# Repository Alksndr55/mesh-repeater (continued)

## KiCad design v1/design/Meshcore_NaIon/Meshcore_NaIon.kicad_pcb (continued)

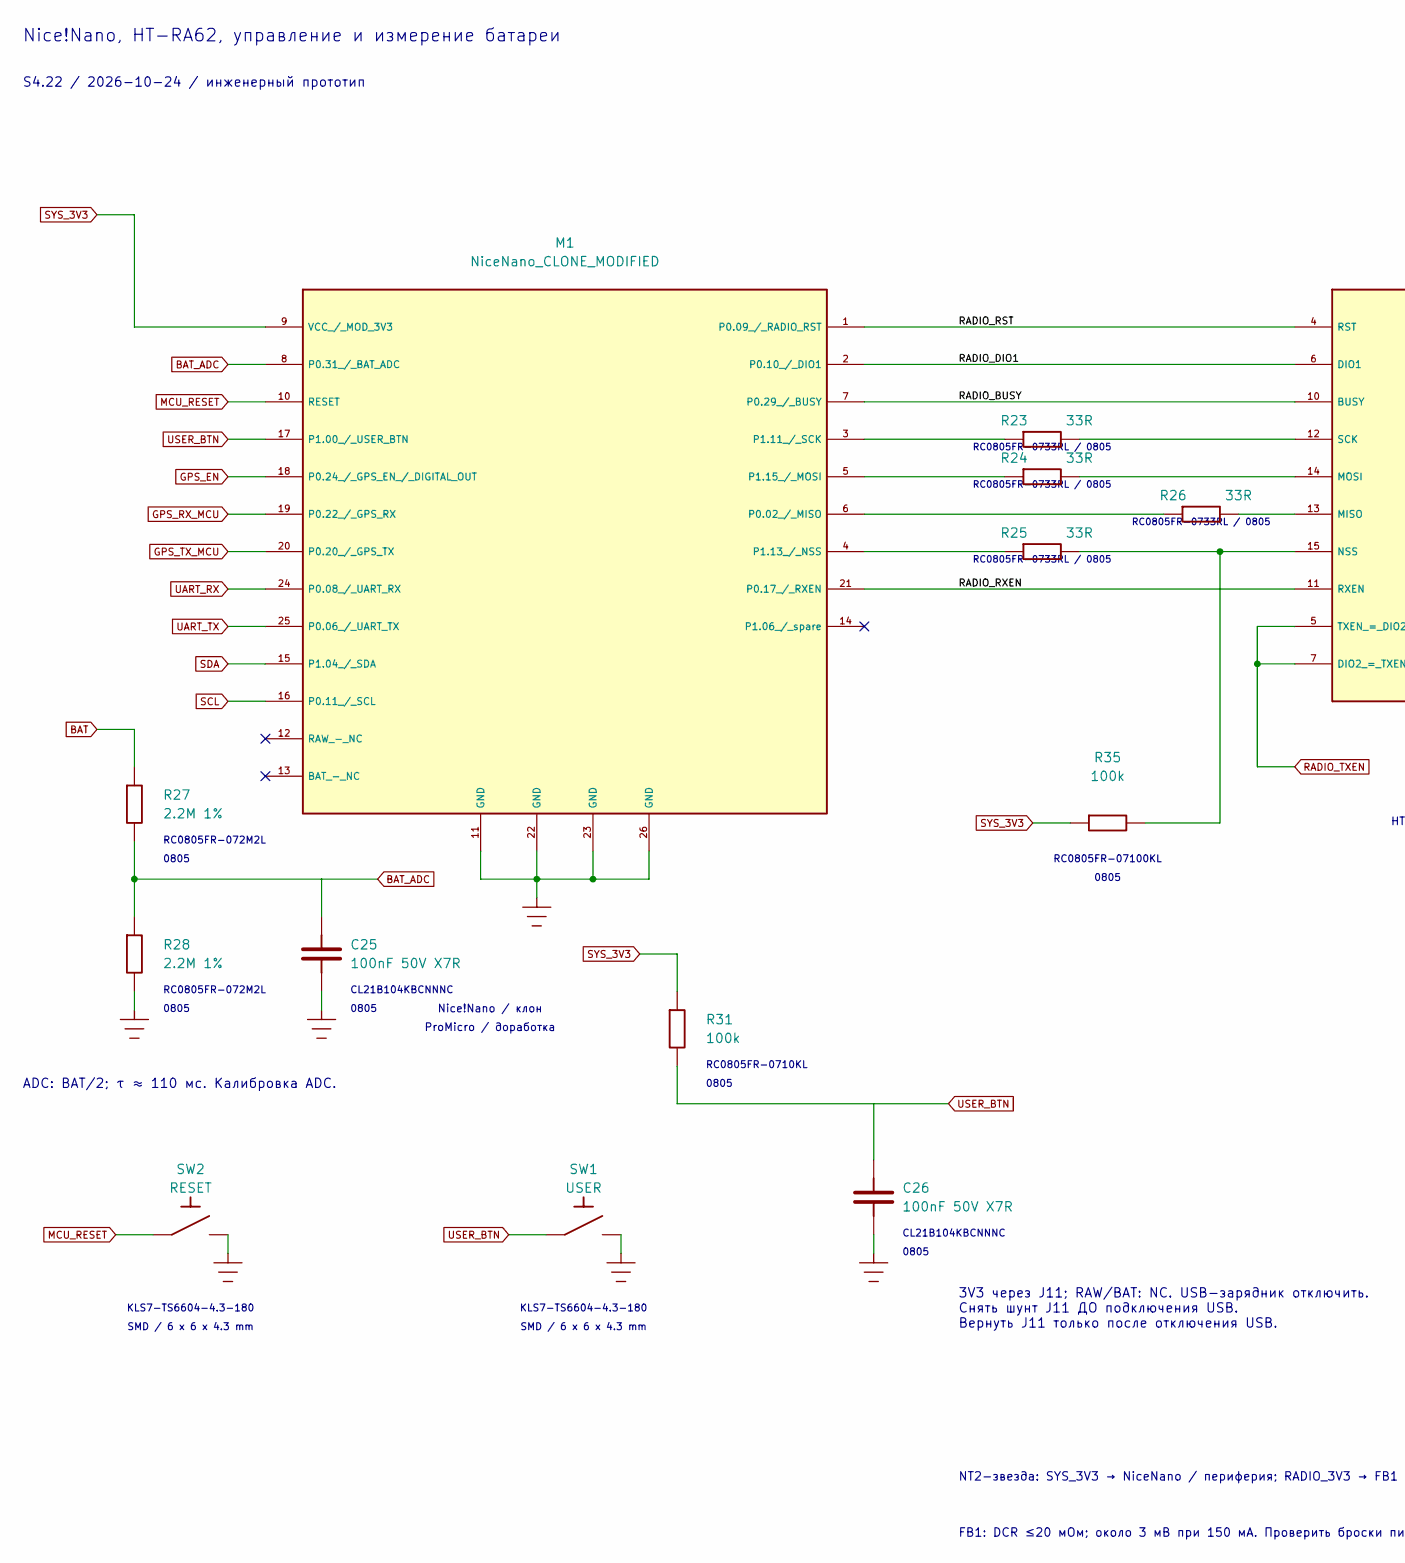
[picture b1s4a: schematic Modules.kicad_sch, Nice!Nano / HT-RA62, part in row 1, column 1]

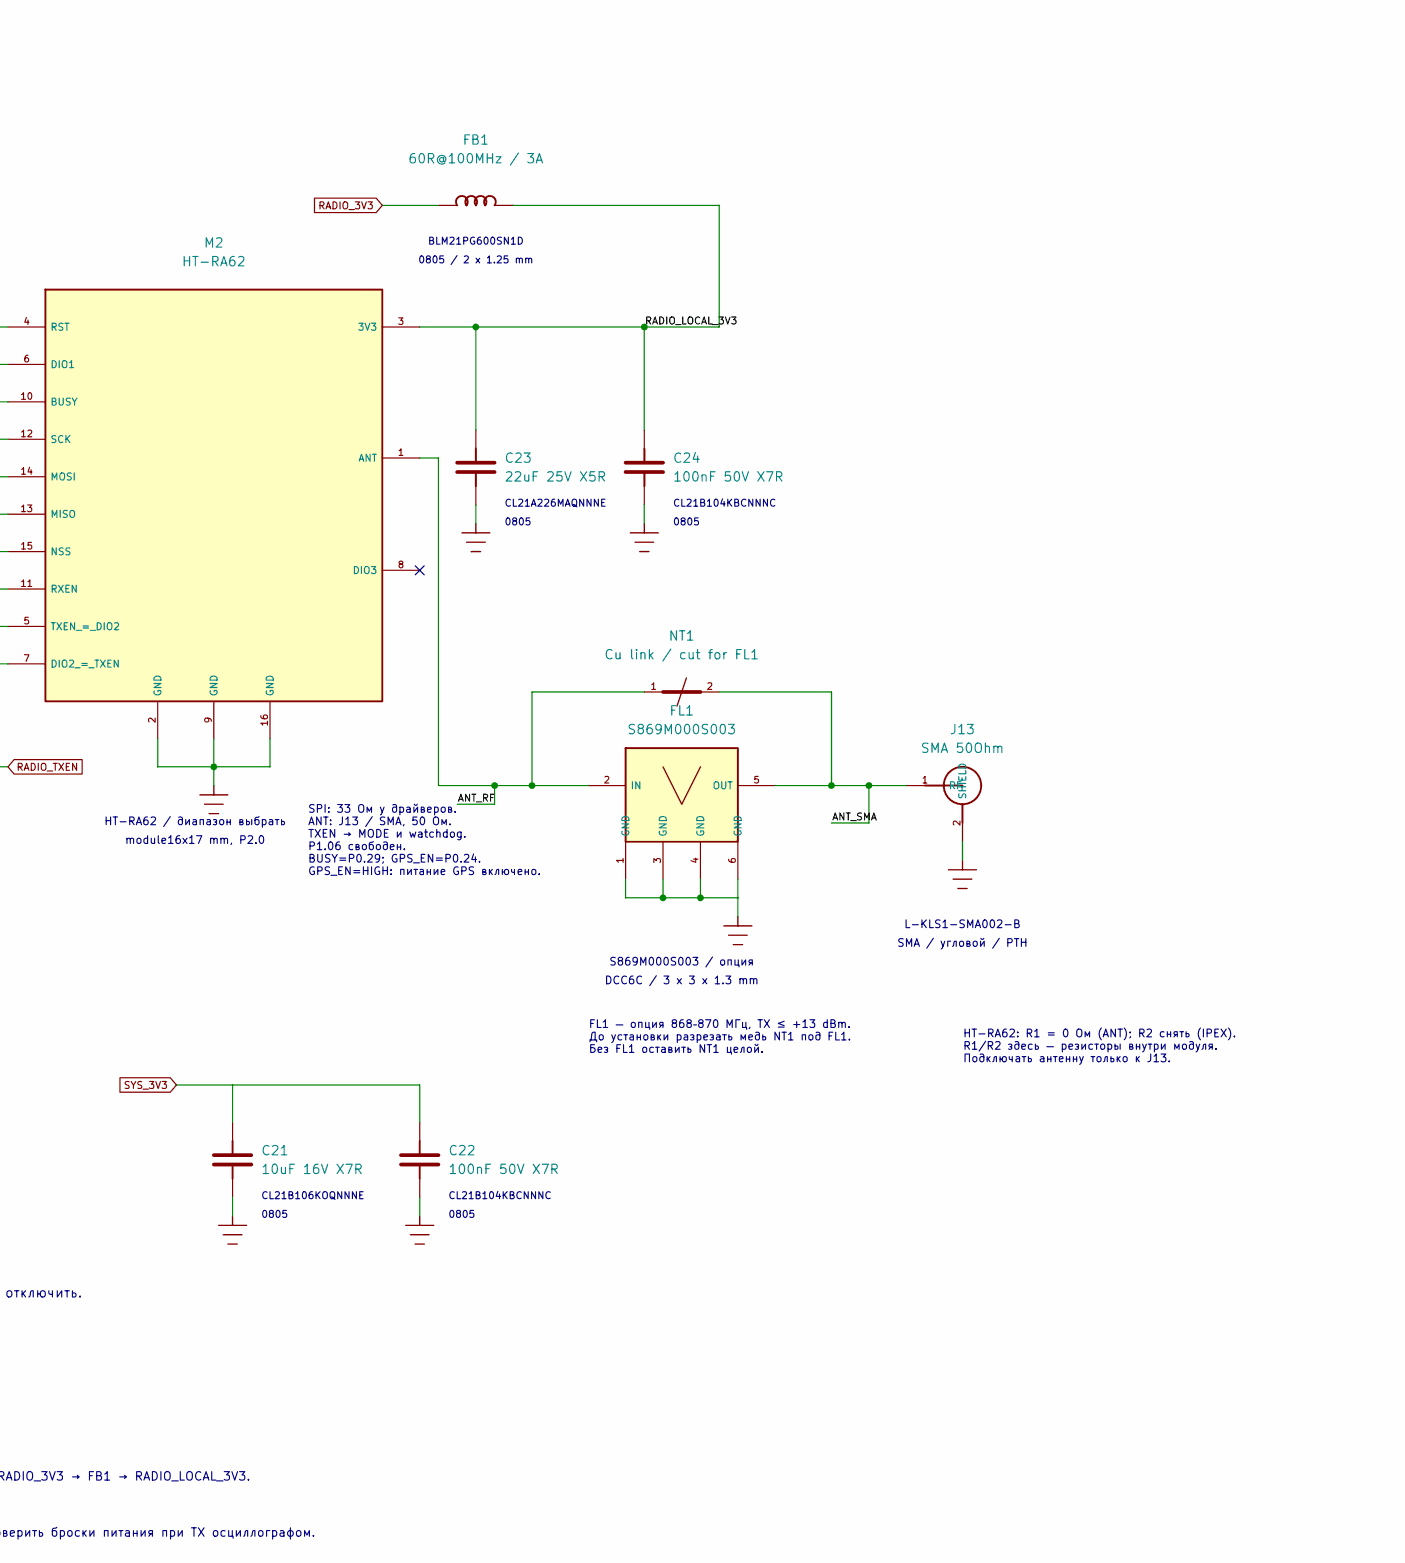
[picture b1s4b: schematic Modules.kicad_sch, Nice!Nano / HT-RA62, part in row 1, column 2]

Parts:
C21: 10uF 16V X7R; C_0805_2012Metric; MPN CL21B106KOQNNNE
C22, C24, C25, C26: 100nF 50V X7R; C_0805_2012Metric; MPN CL21B104KBCNNNC
C23: 22uF 25V X5R; C_0805_2012Metric; MPN CL21A226MAQNNNE
FB1: 60R@100MHz / 3A; Ferrite_Murata_BLM21PG; MPN BLM21PG600SN1D
FL1: S869M000S003; SAW_AEL_DCC6C_S869M000S003; MPN S869M000S003
J13: SMA 50Ohm; SMA_KLS1_SMA002_B_Horizontal; MPN L-KLS1-SMA002-B
M1: NiceNano_CLONE_MODIFIED; NiceNano_13x2_Socket; MPN User supplied NiceNano clone
M2: HT-RA62; HT_RA62; MPN HT-RA62 band variant TBD
NT1: Cu link / cut for FL1; RF_Cut_Link_0p6; MPN PCB copper / not purchased
R23, R24, R25, R26: 33R; R_0805_2012Metric; MPN RC0805FR-0733RL
R27, R28: 2.2M 1%; R_0805_2012Metric; MPN RC0805FR-072M2L
R31, R35: 100k; R_0805_2012Metric; MPN RC0805FR-07100KL
SW1: USER; SW_Push_KLS7_TS6604_4_3_180; MPN KLS7-TS6604-4.3-180
SW2: RESET; SW_Push_KLS7_TS6604_4_3_180; MPN KLS7-TS6604-4.3-180

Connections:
/3. Modules/ANT_RF: FL1.2 (IN), M2.1 (ANT), NT1.1 (A)
/3. Modules/ANT_SMA: FL1.5 (OUT), J13.1 (SIGNAL), NT1.2 (B)
/3. Modules/RADIO_BUSY: M1.7 (P0.29_/_BUSY), M2.10 (BUSY_10)
/3. Modules/RADIO_DIO1: M1.2 (P0.10_/_DIO1), M2.6 (DIO1_6)
/3. Modules/RADIO_LOCAL_3V3: C23.1, C24.1, FB1.2, M2.3 (3V3_3)
/3. Modules/RADIO_RST: M1.1 (P0.09_/_RADIO_RST), M2.4 (RST_4)
/3. Modules/RADIO_RXEN: M1.21 (P0.17_/_RXEN), M2.11 (RXEN_11)
BAT: R27.1; also elsewhere on the board
BAT_ADC: C25.1, M1.8 (P0.31_/_BAT_ADC), R27.2, R28.1
GND: C21.2, C22.2, C23.2, C24.2, C25.2, C26.2, FL1.1 (GND), FL1.3 (GND), FL1.4 (GND), FL1.6 (GND), J13.2 (GND), M1.11 (GND), M1.22 (GND), M1.23 (GND), M1.26 (GND), M2.2 (GND_2), M2.9 (GND_9), M2.16 (GND_16), R28.2, SW1.2, SW2.2; also elsewhere on the board
GPS_EN: M1.18 (P0.24_/_GPS_EN_/_DIGITAL_OUT); also elsewhere on the board
GPS_RX_MCU: M1.19 (P0.22_/_GPS_RX); also elsewhere on the board
GPS_TX_MCU: M1.20 (P0.20_/_GPS_TX); also elsewhere on the board
MCU_RESET: M1.10 (RESET), SW2.1; also elsewhere on the board
unnamed: M1.6 (P0.02_/_MISO), R26.2
unnamed: M1.3 (P1.11_/_SCK), R23.1
unnamed: M1.4 (P1.13_/_NSS), R25.1
unnamed: M1.5 (P1.15_/_MOSI), R24.1
unnamed: M2.13 (MISO_13), R26.1
unnamed: M2.14 (MOSI_14), R24.2
unnamed: M2.15 (NSS_15), R25.2, R35.2
unnamed: M2.12 (SCK_12), R23.2
RADIO_3V3: FB1.1; also elsewhere on the board
RADIO_TXEN: M2.5 (TXEN_=_DIO2_5), M2.7 (DIO2_=_TXEN_7); also elsewhere on the board
SCL: M1.16 (P0.11_/_SCL); also elsewhere on the board
SDA: M1.15 (P1.04_/_SDA); also elsewhere on the board
SYS_3V3: C21.1, C22.1, M1.9 (VCC_/_MOD_3V3), R31.1, R35.1; also elsewhere on the board
UART_RX: M1.24 (P0.08_/_UART_RX); also elsewhere on the board
UART_TX: M1.25 (P0.06_/_UART_TX); also elsewhere on the board
USER_BTN: C26.1, M1.17 (P1.00_/_USER_BTN), R31.2, SW1.1

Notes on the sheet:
FB1: DCR ≤20 мОм; около 3 мВ при 150 мА. Проверить броски питания при TX осциллографом.
HT-RA62: R1 = 0 Ом (ANT); R2 снять (IPEX). R1/R2 здесь — резисторы внутри модуля. Подключать антенну только к J13.
SMA / угловой / PTH
FL1 — опция 868–870 МГц, TX ≤ +13 dBm. До установки разрезать медь NT1 под FL1. Без FL1 оставить NT1 целой.
KLS7-TS6604-4.3-180
BLM21PG600SN1D
0805
RC0805FR-0733RL / 0805
SMD / 6 x 6 x 4.3 mm
module16x17 mm, P2.0
S869M000S003 / опция
CL21B104KBCNNNC
CL21B106KOQNNNE
SPI: 33 Ом у драйверов. ANT: J13 / SMA, 50 Ом. TXEN → MODE и watchdog. P1.06 свободен. BUSY=P0.29; GPS_EN=P0.24. GPS_EN=HIGH: питание GPS включено.
DCC6C / 3 x 3 x 1.3 mm
3V3 через J11; RAW/BAT: NC. USB-зарядник отключить. Снять шунт J11 ДО подключения USB. Вернуть J11 только после отключения USB.
L-KLS1-SMA002-B
ADC: BAT/2; τ ≈ 110 мс. Калибровка ADC.
Nice!Nano, HT-RA62, управление и измерение батареи
S4.22 / 2026-10-24 / инженерный прототип
CL21A226MAQNNNE
RC0805FR-072M2L
HT-RA62 / диапазон выбрать
NT2-звезда: SYS_3V3 → NiceNano / периферия; RADIO_3V3 → FB1 → RADIO_LOCAL_3V3.
RC0805FR-0710KL
Nice!Nano / клон
RC0805FR-07100KL
ProMicro / доработка
0805 / 2 x 1.25 mm

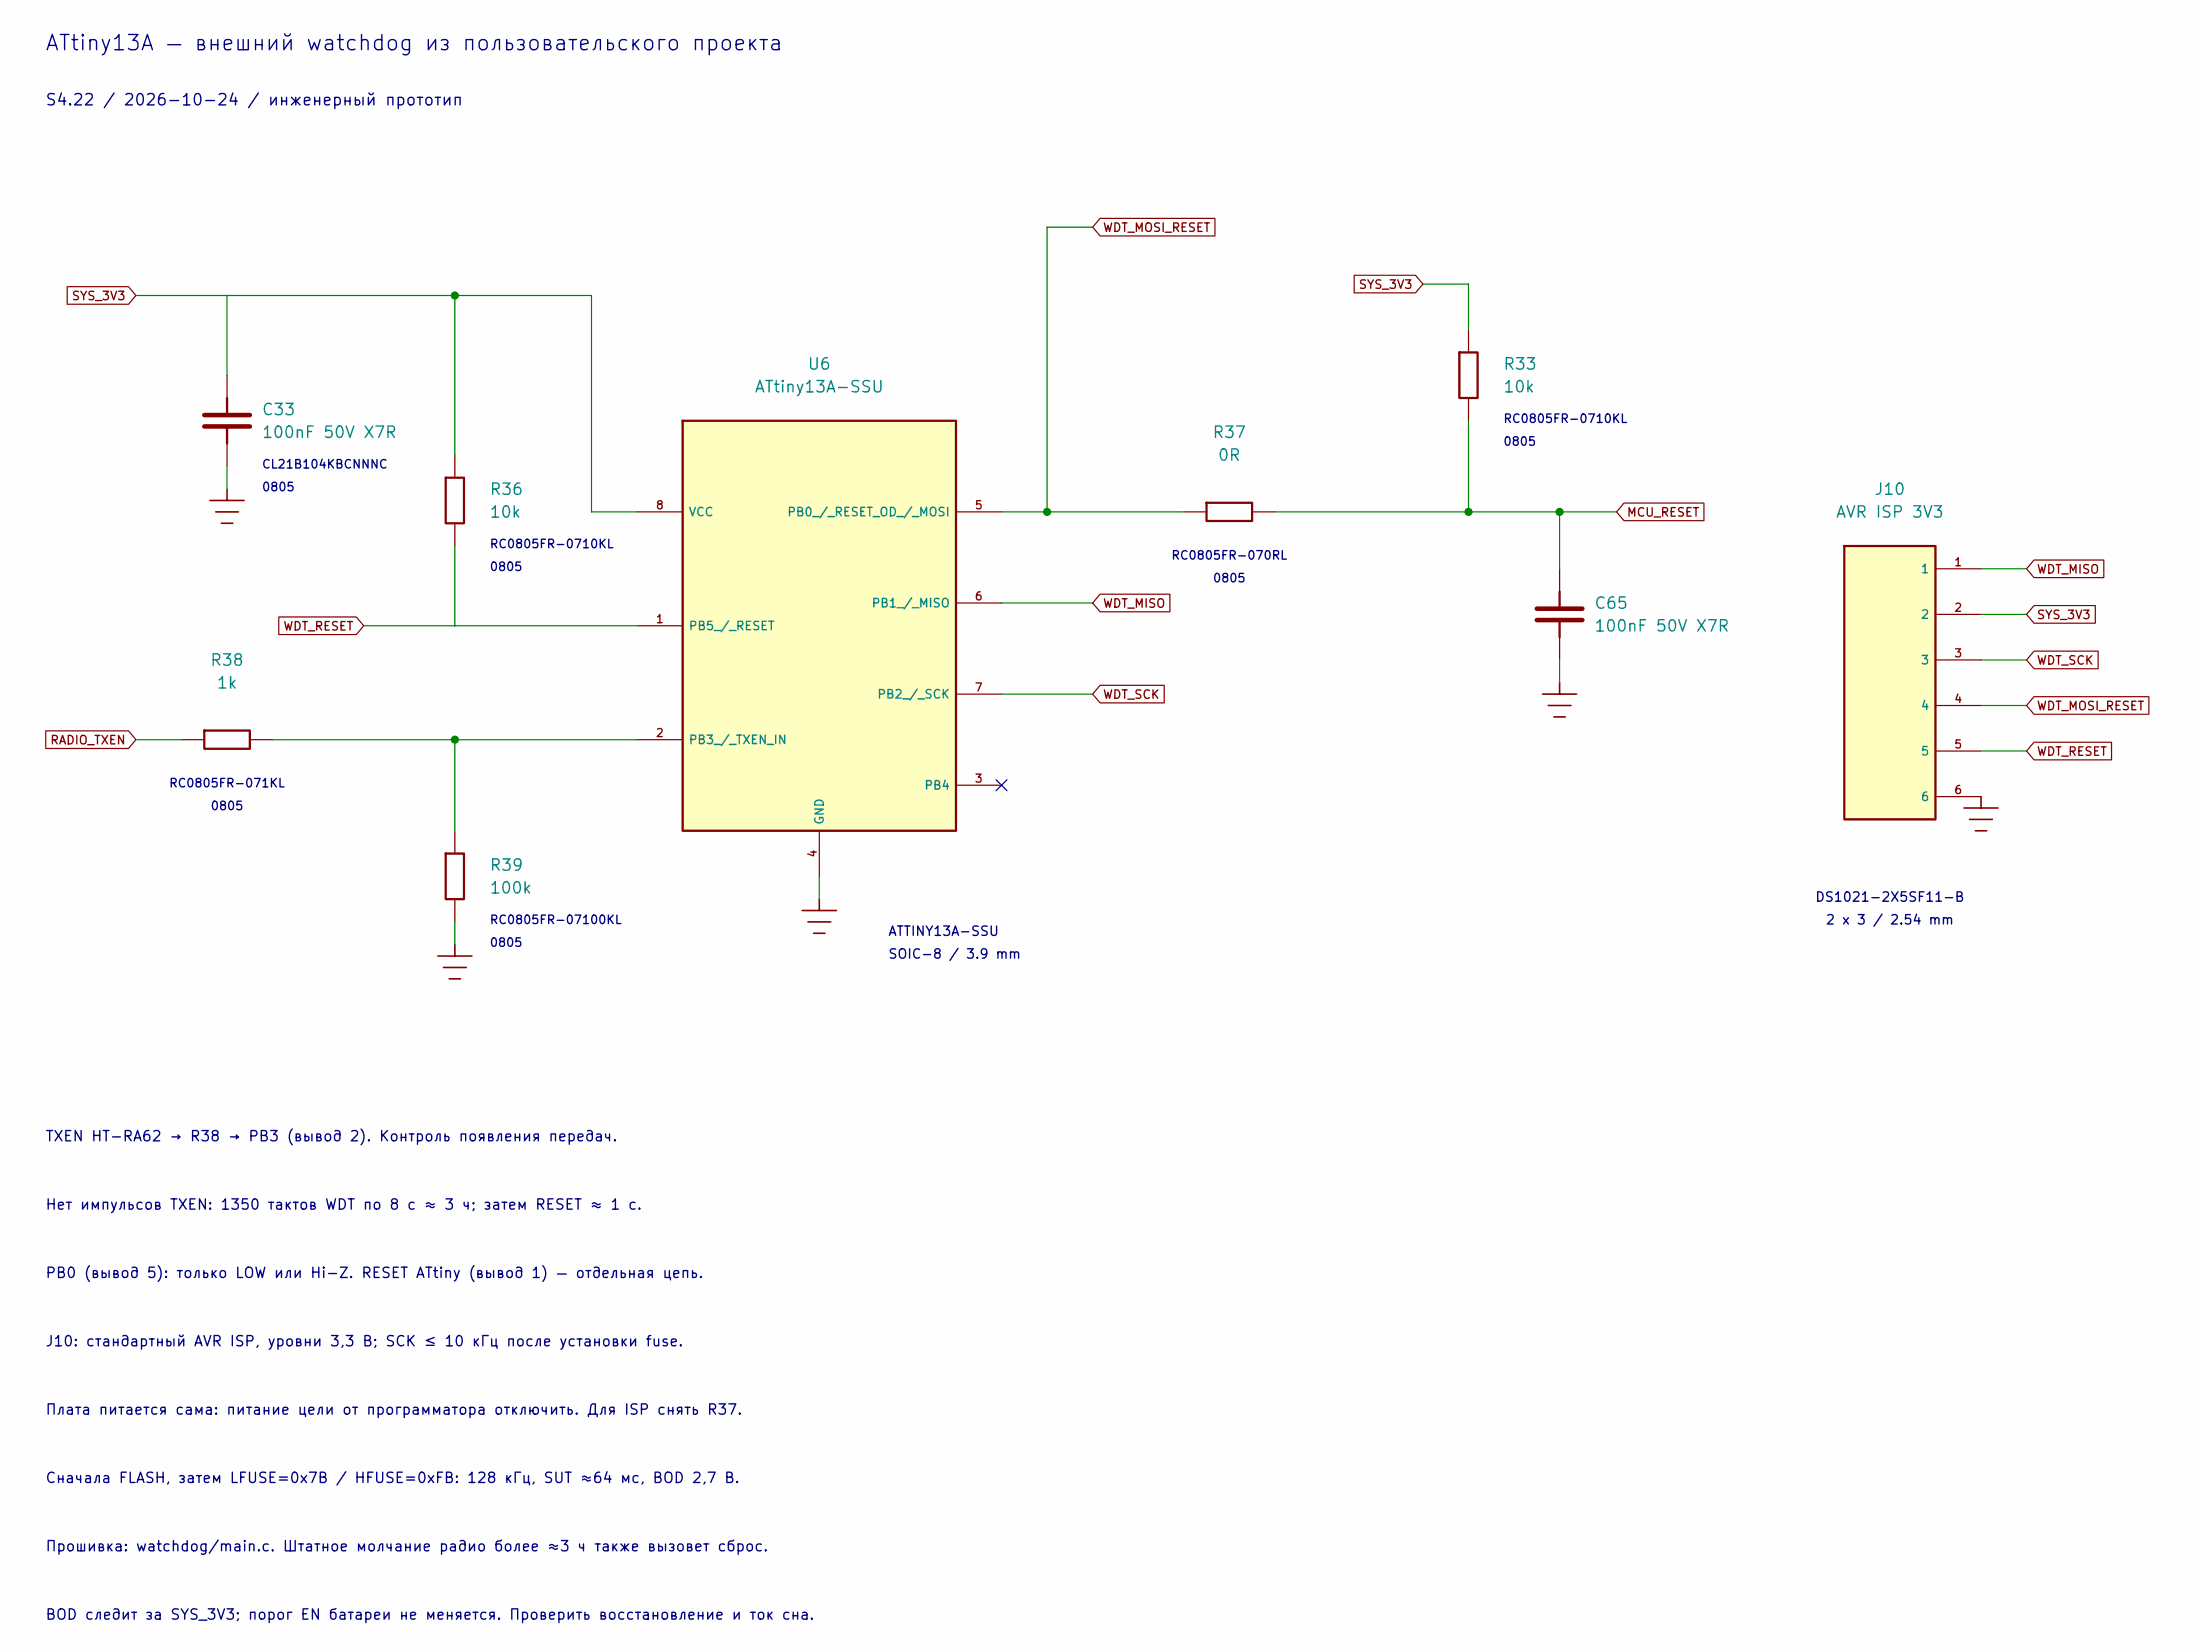
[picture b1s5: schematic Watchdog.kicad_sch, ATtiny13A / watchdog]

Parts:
C33, C65: 100nF 50V X7R; C_0805_2012Metric; MPN CL21B104KBCNNNC
J10: AVR ISP 3V3; PinHeader_2x03_P2.54mm_Vertical; MPN DS1021-2X5SF11-B
R33, R36: 10k; R_0805_2012Metric; MPN RC0805FR-0710KL
R37: 0R; R_0805_2012Metric; MPN RC0805FR-070RL
R38: 1k; R_0805_2012Metric; MPN RC0805FR-071KL
R39: 100k; R_0805_2012Metric; MPN RC0805FR-07100KL
U6: ATtiny13A-SSU; SOIC-8_3.9x4.9mm_P1.27mm; MPN ATTINY13A-SSU

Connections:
GND: C33.2, C65.2, J10.6, R39.2, U6.4 (GND); also elsewhere on the board
MCU_RESET: C65.1, R33.2, R37.2; also elsewhere on the board
unnamed: R38.2, R39.1, U6.2 (PB3_/_TXEN_IN)
RADIO_TXEN: R38.1; also elsewhere on the board
SYS_3V3: C33.1, J10.2, R33.1, R36.1, U6.8 (VCC); also elsewhere on the board
WDT_MISO: J10.1, U6.6 (PB1_/_MISO)
WDT_MOSI_RESET: J10.4, R37.1, U6.5 (PB0_/_RESET_OD_/_MOSI)
WDT_RESET: J10.5, R36.2, U6.1 (PB5_/_RESET)
WDT_SCK: J10.3, U6.7 (PB2_/_SCK)

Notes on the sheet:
PB0 (вывод 5): только LOW или Hi-Z. RESET ATtiny (вывод 1) — отдельная цепь.
ATtiny13A — внешний watchdog из пользовательского проекта
0805
RC0805FR-07100KL
Плата питается сама: питание цели от программатора отключить. Для ISP снять R37.
RC0805FR-070RL
SOIC-8 / 3.9 mm
TXEN HT-RA62 → R38 → PB3 (вывод 2). Контроль появления передач.
ATTINY13A-SSU
J10: стандартный AVR ISP, уровни 3,3 В; SCK ≤ 10 кГц после установки fuse.
DS1021-2X5SF11-B
BOD следит за SYS_3V3; порог EN батареи не меняется. Проверить восстановление и ток сна.
CL21B104KBCNNNC
RC0805FR-071KL
RC0805FR-0710KL
Сначала FLASH, затем LFUSE=0x7B / HFUSE=0xFB: 128 кГц, SUT ≈64 мс, BOD 2,7 В.
S4.22 / 2026-10-24 / инженерный прототип
2 x 3 / 2.54 mm
Прошивка: watchdog/main.c. Штатное молчание радио более ≈3 ч также вызовет сброс.
Нет импульсов TXEN: 1350 тактов WDT по 8 с ≈ 3 ч; затем RESET ≈ 1 с.

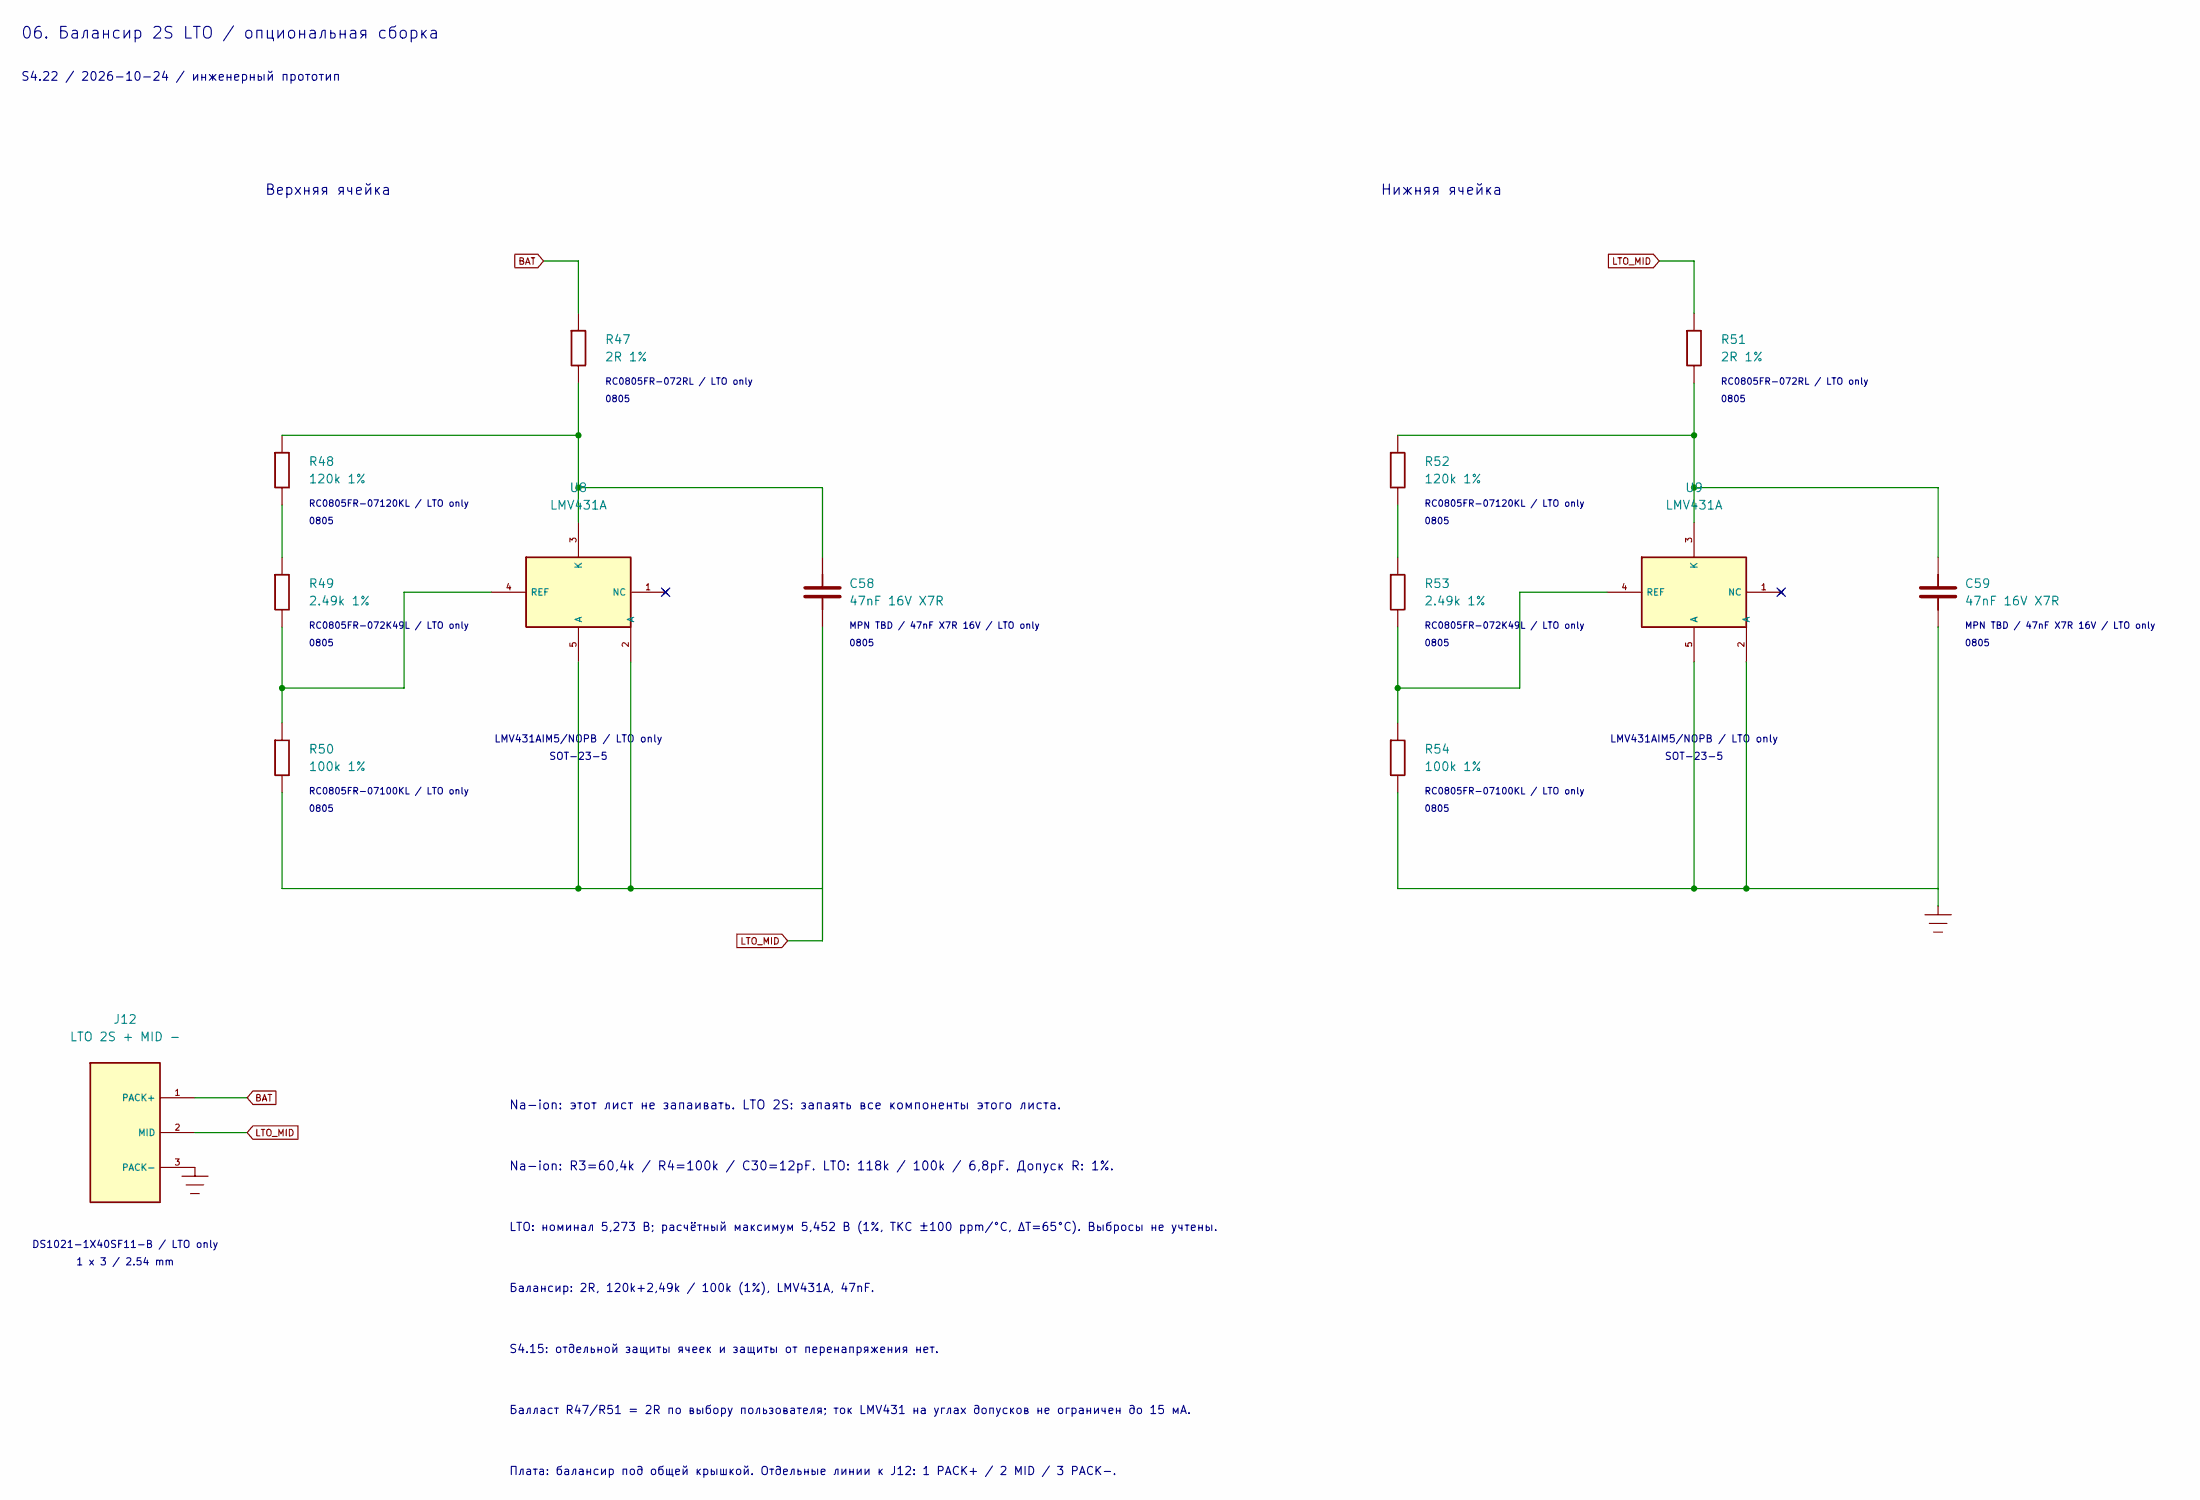
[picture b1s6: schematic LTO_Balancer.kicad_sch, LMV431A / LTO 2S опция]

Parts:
C58, C59: 47nF 16V X7R; C_0805_2012Metric; MPN MPN TBD / 47nF X7R 16V
J12: LTO 2S + MID -; PinHeader_1x03_P2.54mm_Vertical; MPN DS1021-1X40SF11-B
R47, R51: 2R 1%; R_0805_2012Metric; MPN RC0805FR-072RL; LCSC C110775
R48, R52: 120k 1%; R_0805_2012Metric; MPN RC0805FR-07120KL; LCSC C110775
R49, R53: 2.49k 1%; R_0805_2012Metric; MPN RC0805FR-072K49L; LCSC C110775
R50, R54: 100k 1%; R_0805_2012Metric; MPN RC0805FR-07100KL; LCSC C110775
U8, U9: LMV431A; SOT-23-5; MPN LMV431AIM5/NOPB

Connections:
BAT: J12.1 (PACK+), R47.1; also elsewhere on the board
GND: C59.2, J12.3 (PACK-), R54.2, U9.2 (A), U9.5 (A); also elsewhere on the board
LTO_MID: C58.2, J12.2 (MID), R50.2, R51.1, U8.2 (A), U8.5 (A)
unnamed: R48.2, R49.1
unnamed: R52.2, R53.1
unnamed: C58.1, R47.2, R48.1, U8.3 (K)
unnamed: R49.2, R50.1, U8.4 (REF)
unnamed: C59.1, R51.2, R52.1, U9.3 (K)
unnamed: R53.2, R54.1, U9.4 (REF)

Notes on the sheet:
0805
LMV431AIM5/NOPB / LTO only
MPN TBD / 47nF X7R 16V / LTO only
RC0805FR-07120KL / LTO only
RC0805FR-072K49L / LTO only
SOT-23-5
RC0805FR-07100KL / LTO only
1 x 3 / 2.54 mm
Верхняя ячейка
S4.15: отдельной защиты ячеек и защиты от перенапряжения нет.
S4.22 / 2026-10-24 / инженерный прототип
06. Балансир 2S LTO / опциональная сборка
Балансир: 2R, 120k+2,49k / 100k (1%), LMV431A, 47nF.
RC0805FR-072RL / LTO only
Плата: балансир под общей крышкой. Отдельные линии к J12: 1 PACK+ / 2 MID / 3 PACK-.
LTO: номинал 5,273 В; расчётный максимум 5,452 В (1%, ТКС ±100 ppm/°C, ΔT=65°C). Выбросы не учтены.
Нижняя ячейка
DS1021-1X40SF11-B / LTO only
Балласт R47/R51 = 2R по выбору пользователя; ток LMV431 на углах допусков не ограничен до 15 мА.
Na-ion: R3=60,4k / R4=100k / C30=12pF. LTO: 118k / 100k / 6,8pF. Допуск R: 1%.
Na-ion: этот лист не запаивать. LTO 2S: запаять все компоненты этого листа.

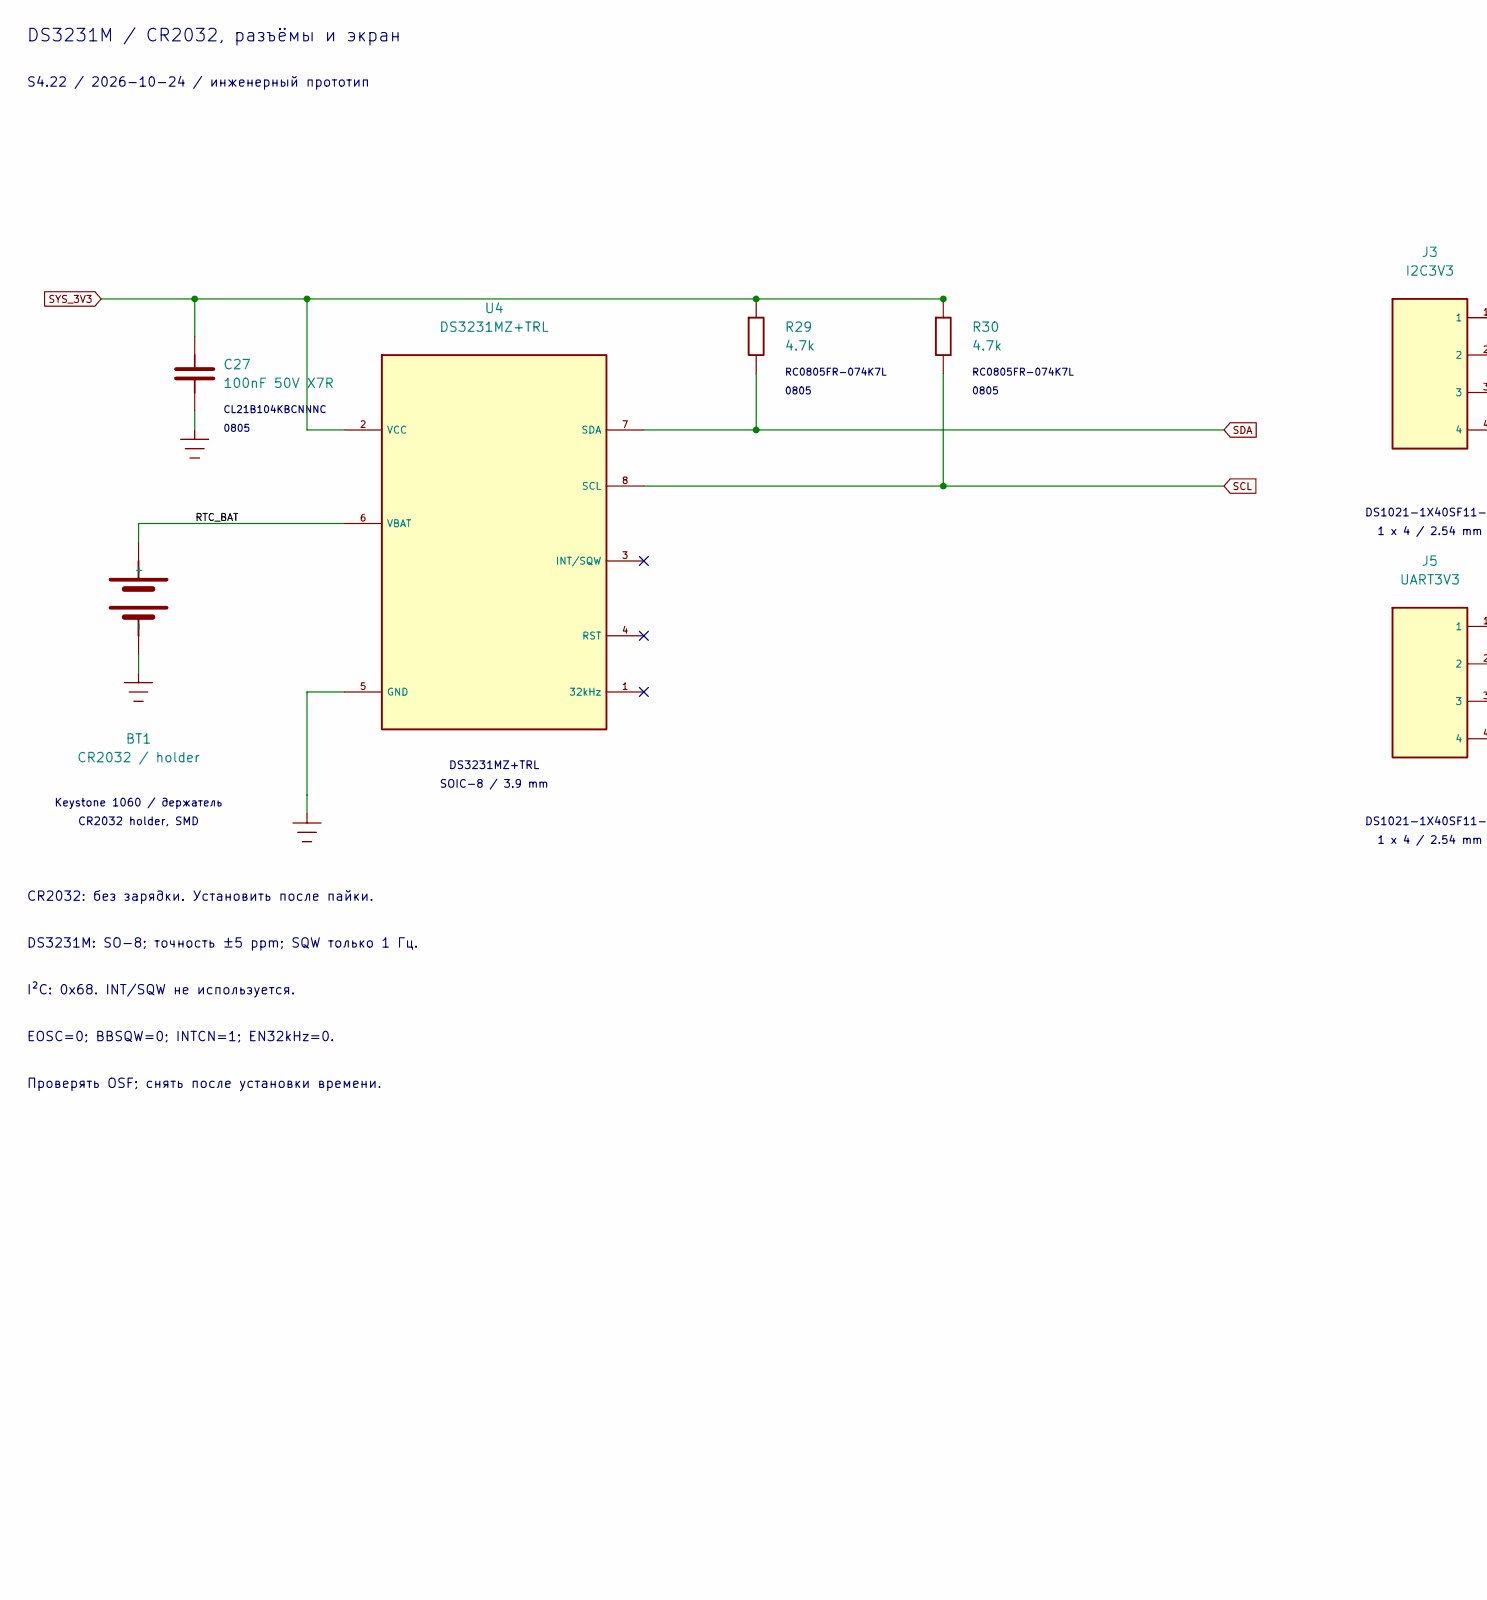
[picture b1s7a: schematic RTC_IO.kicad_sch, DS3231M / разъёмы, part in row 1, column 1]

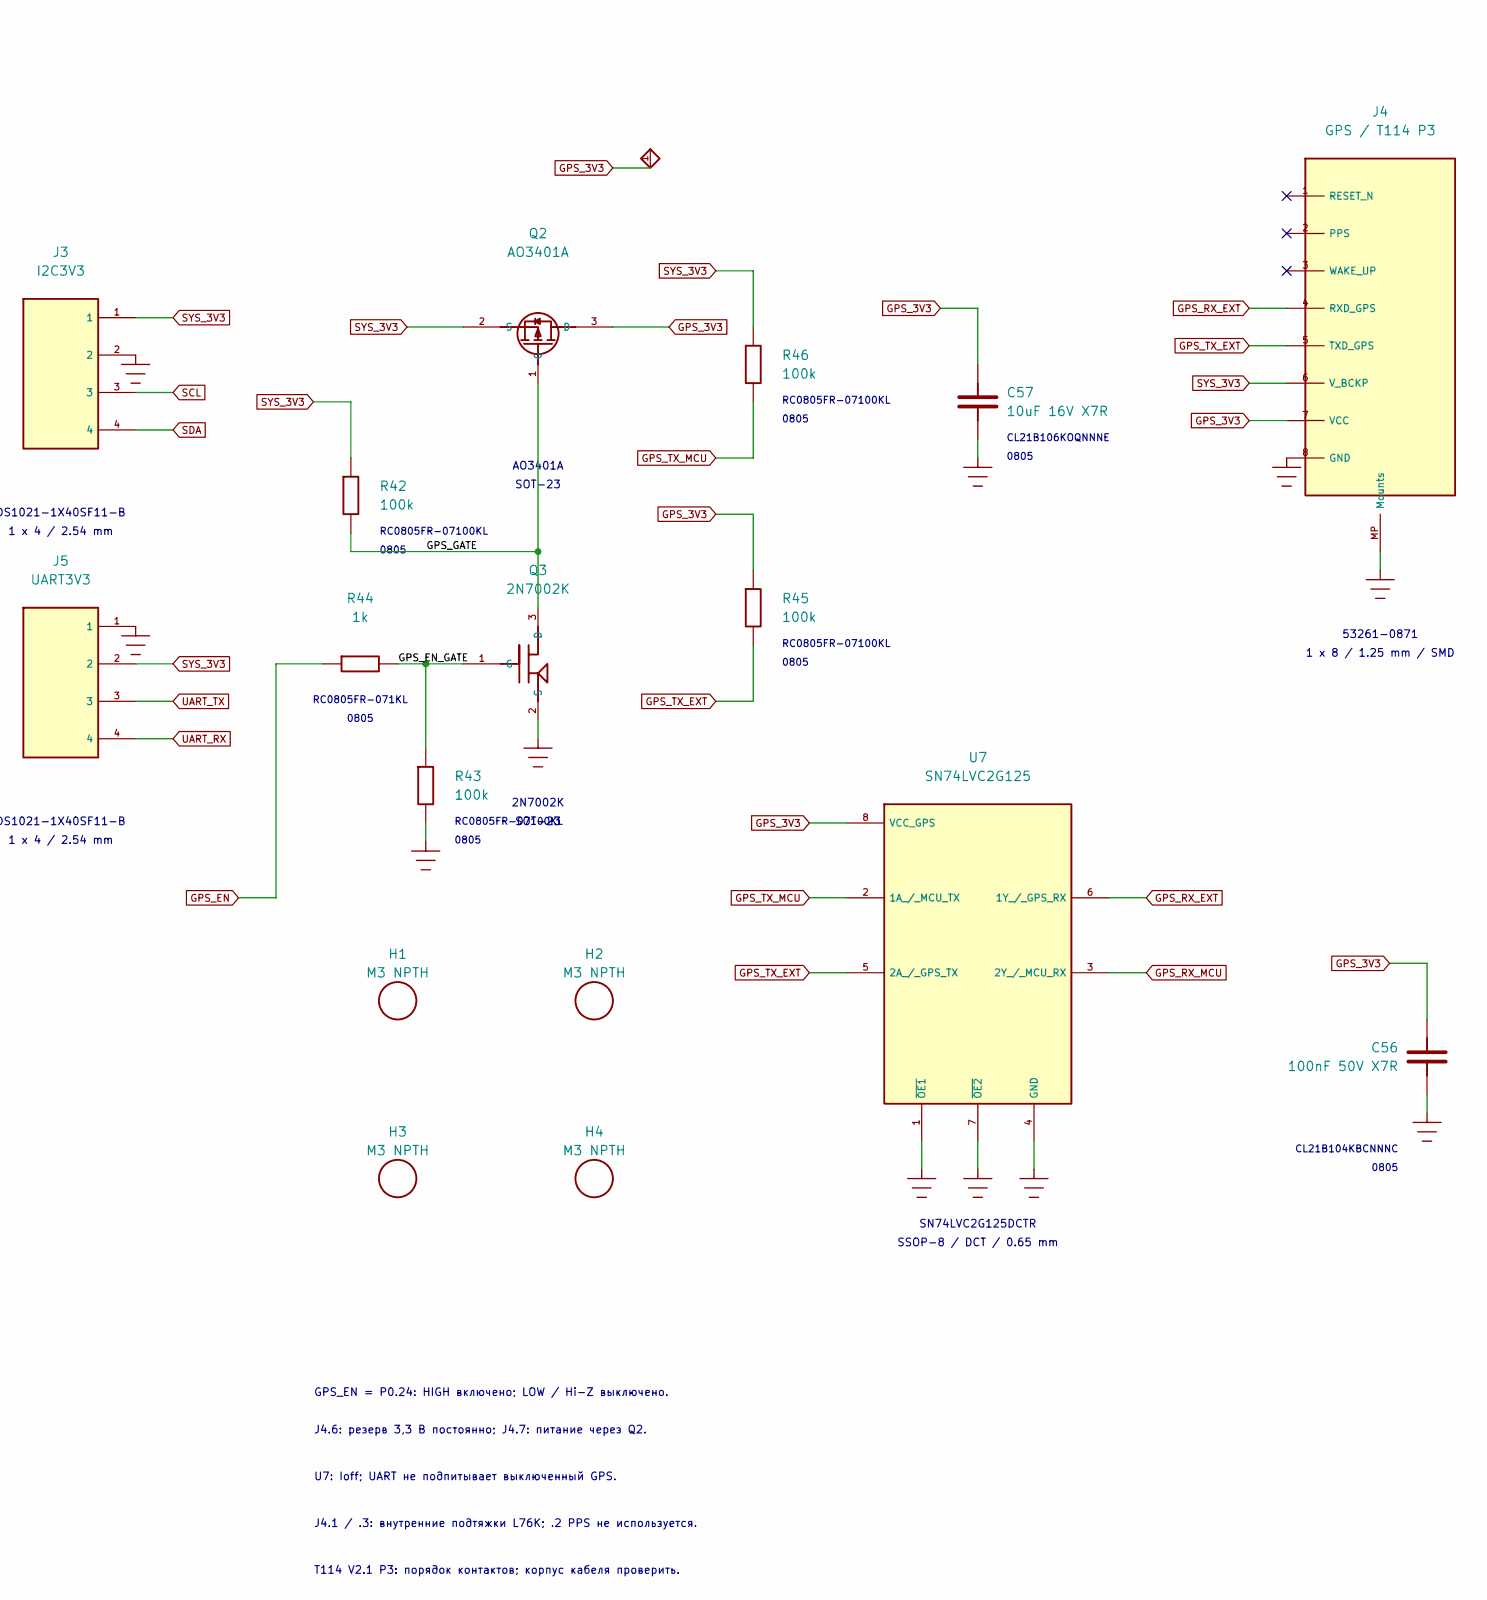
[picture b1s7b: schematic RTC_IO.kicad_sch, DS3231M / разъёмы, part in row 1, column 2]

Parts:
BT1: CR2032 / holder; BatteryHolder_Keystone_1060_1x2032; MPN 1060; LCSC C5370859
C27, C56: 100nF 50V X7R; C_0805_2012Metric; MPN CL21B104KBCNNNC
C57: 10uF 16V X7R; C_0805_2012Metric; MPN CL21B106KOQNNNE
H1, H2, H3, H4: M3 NPTH; MountingHole_3.2mm_M3
J3: I2C3V3; PinHeader_1x04_P2.54mm_Vertical; MPN DS1021-1X40SF11-B
J4: GPS / T114 P3; Molex_PicoBlade_53261-0871_1x08-1MP_P1.25mm_Horizontal; MPN 53261-0871
J5: UART3V3; PinHeader_1x04_P2.54mm_Vertical; MPN DS1021-1X40SF11-B
Q2: AO3401A; SOT-23; MPN AO3401A
Q3: 2N7002K; SOT-23; MPN 2N7002K
R29, R30: 4.7k; R_0805_2012Metric; MPN RC0805FR-074K7L
R42, R43, R45, R46: 100k; R_0805_2012Metric; MPN RC0805FR-07100KL
R44: 1k; R_0805_2012Metric; MPN RC0805FR-071KL
U4: DS3231MZ+TRL; SOIC-8_3.9x4.9mm_P1.27mm; MPN DS3231MZ+TRL
U7: SN74LVC2G125; TI_DCT0008A; MPN SN74LVC2G125DCTR

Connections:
/4. RTC_IO/GPS_EN_GATE: Q3.1 (G), R43.1, R44.2
/4. RTC_IO/GPS_GATE: Q2.1 (G), Q3.3 (D), R42.2
/4. RTC_IO/RTC_BAT: BT1.1 (+), U4.6 (VBAT)
GND: BT1.2 (-), C27.2, C56.2, C57.2, J3.2, J4.8 (GND), J4.MP (Mounts), J5.1, Q3.2 (S), R43.2, U4.5 (GND), U7.1 (~OE1), U7.4 (GND), U7.7 (~OE2); also elsewhere on the board
GPS_3V3: C56.1, C57.1, J4.7 (VCC), Q2.3 (D), R45.1, U7.8 (VCC_GPS)
GPS_EN: R44.1; also elsewhere on the board
GPS_RX_EXT: J4.4 (RXD_GPS), U7.6 (1Y_/_GPS_RX)
GPS_RX_MCU: U7.3 (2Y_/_MCU_RX); also elsewhere on the board
GPS_TX_EXT: J4.5 (TXD_GPS), R45.2, U7.5 (2A_/_GPS_TX)
GPS_TX_MCU: R46.2, U7.2 (1A_/_MCU_TX); also elsewhere on the board
SCL: J3.3, R30.2, U4.8 (SCL); also elsewhere on the board
SDA: J3.4, R29.2, U4.7 (SDA); also elsewhere on the board
SYS_3V3: C27.1, J3.1, J4.6 (V_BCKP), J5.2, Q2.2 (S), R29.1, R30.1, R42.1, R46.1, U4.2 (VCC); also elsewhere on the board
UART_RX: J5.4; also elsewhere on the board
UART_TX: J5.3; also elsewhere on the board

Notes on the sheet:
Проверять OSF; снять после установки времени.
J4.6: резерв 3,3 В постоянно; J4.7: питание через Q2.
SOT-23
T114 V2.1 P3: порядок контактов; корпус кабеля проверить.
U7: Ioff; UART не подпитывает выключенный GPS.
AO3401A
0805
1 x 4 / 2.54 mm
CL21B104KBCNNNC
RC0805FR-07100KL
DS3231M / CR2032, разъёмы и экран
S4.22 / 2026-10-24 / инженерный прототип
CR2032: без зарядки. Установить после пайки.
RC0805FR-074K7L
J4.1 / .3: внутренние подтяжки L76K; .2 PPS не используется.
1 x 8 / 1.25 mm / SMD
Keystone 1060 / держатель
CR2032 holder, SMD
DS1021-1X40SF11-B
DS3231M: SO-8; точность ±5 ppm; SQW только 1 Гц.
SSOP-8 / DCT / 0.65 mm
SN74LVC2G125DCTR
EOSC=0; BBSQW=0; INTCN=1; EN32kHz=0.
53261-0871
GPS_EN = P0.24: HIGH включено; LOW / Hi-Z выключено.
RC0805FR-071KL
CL21B106KOQNNNE
2N7002K
I²C: 0x68. INT/SQW не используется.
DS3231MZ+TRL
SOIC-8 / 3.9 mm
